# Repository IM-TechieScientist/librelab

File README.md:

# LibreLab

LibreLab is a low-cost, open lab instrument for embedded developers: part logic analyser, part mixed-signal scope, part signal generator, part protocol workbench. The goal is simple: make the kind of debug workflow people buy premium USB instruments for available as open hardware and open software at student/hacker-lab pricing.

Current hardware is targeting a PCB+BOM cost below `₹2500`, roughly `$26.4` at recent INR/USD rates. The next hardware revision is targeting a sub-`$50` build with RP2350B, an AD9629-class high-speed ADC path, HSTX-based high-speed data movement toward a USB 3-class host link, and generous PSRAM buffering.

## Hardware Preview

<table>
  <tr>
    <td width="33%"></td>
    <td width="33%"></td>
    <td width="33%"></td>
  </tr>
  <tr>
    <td align="center">v0.9 board render</td>
    <td align="center">fabricated PCB stack</td>
    <td align="center">PCB top side</td>
  </tr>
</table>

## Software Preview

## Why This Is Interesting

Saleae's current Logic 8 is an 8-channel USB analyser rated at up to 100 MS/s digital capture, 10 MS/s analog capture, 10-bit analog resolution, long PC-streamed captures, 25+ protocol decoders, trigger/search, measurements, automation, and cross-platform software.

LibreLab is aiming at that workflow from the other side of the cost curve:

- `150 MSPS` logic capture on the current RP2350 design path.
- `200 MSPS` logic capture under active development.
- `400 MSPS` burst-mode capture under active development.
- Logic analyser, oscilloscope, mixed-signal capture, pattern generation, test outputs, and bus gateways in one firmware stack.
- USB CDC SCPI today, with optional ESP32-C3 Wi-Fi bridge transport.
- First-party modern desktop software plus PulseView/libsigrok integration for people who prefer the classic sigrok workflow.
- Roadmap hardware aimed at high-speed analog capture and deeper buffering while staying below `$50`.

The bet is that a carefully designed RP2350-class instrument can be brutally useful for firmware bring-up, protocol debugging, education, and small-lab automation without needing a $500-class box on every desk.

## Current Firmware

The firmware lives in [firmware](firmware/) and currently targets Pico 2/RP2350A. Firmware was originally developed by me as part of GSoC 2026.

Implemented so far:

- SCPI 1999-style command interface over USB CDC.
- 1-8 channel PIO/DMA logic analyser.
- One-channel RP2350 internal-ADC oscilloscope path.
- Synchronized mixed-signal one-shot capture.
- 1-8 channel digital pattern generator.
- UART and I2C bus gateways.
- SPI gateway code path, with a known bus-number mismatch still to fix.
- Square-wave and PWM-based analog test outputs.
- ESP32-C3 bridge firmware for TCP SCPI, UDP capture frames, SoftAP provisioning, and mDNS.
- Out-of-tree libsigrok/PulseView driver source.

Useful docs:

- [Firmware README](firmware/README.md)
- [Firmware architecture](firmware/docs/architecture.md)
- [SCPI command reference](firmware/docs/scpi-reference.md)
- [Hardware resources](firmware/docs/hardware.md)
- [RP2350B migration plan](firmware/docs/rp2350b-migration.md)

## Current Software

The desktop application lives in [software](software/) and is built with Electron, React, and TypeScript.

Implemented so far:

- Saleae-style capture workspace with channel rail, session tabs, timeline canvas, and right-side inspector.
- Logic, scope, and mixed-signal modes.
- Deterministic simulator device, so the GUI can be tested without hardware.
- Digital and analog waveform rendering with zoom, pan, fit, hover cursor, and A/B markers.
- Analyzer, measurement, output, and bus-console panels.
- Simulated I2C annotation lane using the same annotation model planned for libsigrokdecode.
- Unit, component, build, and GUI smoke tests.

More:

- [Software README](software/README.md)
- [Software architecture](software/docs/architecture.md)
- [Software feature map](software/docs/features.md)
- [Software testing](software/docs/testing.md)

Run it:

```bash
cd software
npm install
npm run dev
```

Run the browser-rendered GUI for quick UI work:

```bash
cd software
npm run dev:renderer -- --host 127.0.0.1
```

## Hardware Snapshot

The KiCad project lives in [pcb/librelab](pcb/librelab/). The current schematic/PCB includes:

- Raspberry Pi Pico module footprint.
- ESP32-C3-WROOM-02 wireless bridge module.
- AMS1117-3.3 regulator.
- Logic analyser headers.
- Pattern-generator headers.
- ADC headers.
- I2C headers.
- Function/test-output headers.
- Ground headers and reset/boot buttons.
- Generated fabrication outputs under `pcb/librelab/output/`.

## Roadmap

Near-term:

- Connect LibreLab Studio to the real USB SCPI firmware.
- Add capture import/export formats.
- Wire libsigrokdecode into a worker so GUI protocol annotations come from real decoders.
- Finish the SPI gateway bus-number fix.
- Keep PulseView support working alongside the first-party app.

Hardware vNext:

- RP2350B for a cleaner, conflict-free pin map.
- AD9629-class external ADC frontend for serious analog capture.
- HSTX-based high-speed data path toward USB 3-class streaming.
- PSRAM-backed captures and burst buffering.
- 200 MSPS sustained logic capture target and 400 MSPS burst experiments.
- Sub-`$50` target cost.

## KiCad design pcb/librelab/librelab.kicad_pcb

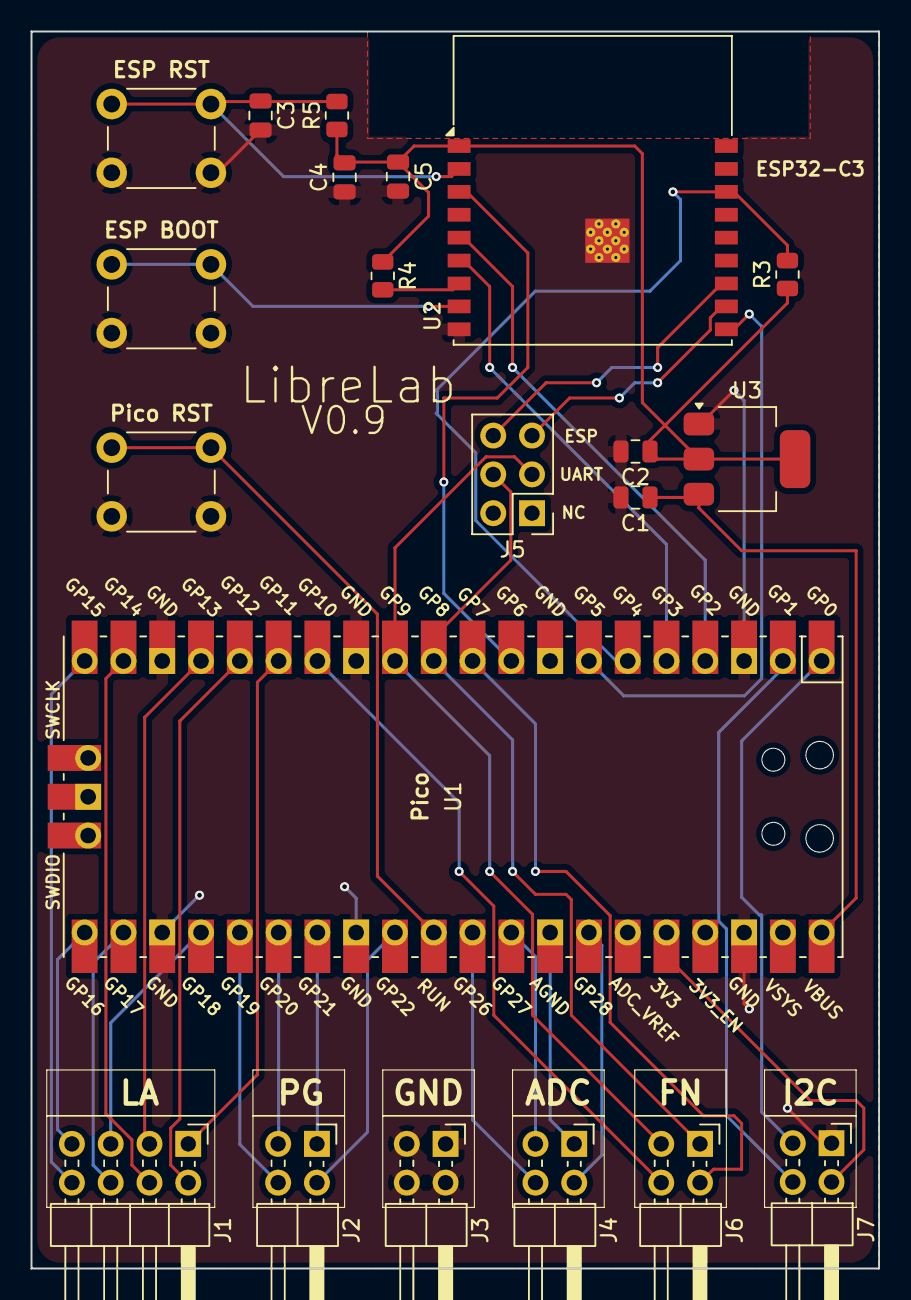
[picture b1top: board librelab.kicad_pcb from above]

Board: 2 copper layers, 55.5 x 81.0 mm, 21 parts (0 on the bottom side), 36 nets.

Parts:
C1, C2, C5: 10uF; C_0805_2012Metric
C3: 1uF; C_0805_2012Metric
C4: 100n; C_0805_2012Metric
ESP BOOT: SW_Push; SW_PUSH_6mm_H5mm
ESP RST: SW_Push; SW_PUSH_6mm_H5mm
J1: LA headers; PinHeader_2x04_P2.54mm_Horizontal
J2: PG headers; PinHeader_2x02_P2.54mm_Horizontal
J3: GND headers; PinHeader_2x02_P2.54mm_Horizontal
J4: ADC headers; PinHeader_2x02_P2.54mm_Horizontal
J5: Conn_02x03_Counter_Clockwise; PinHeader_2x03_P2.54mm_Vertical
J6: FN headers; PinHeader_2x02_P2.54mm_Horizontal
J7: I2C headers; PinHeader_2x02_P2.54mm_Horizontal
Pico RST: SW_Push; SW_PUSH_6mm_H5mm
R3, R4, R5: 10k; R_0805_2012Metric
U1: Pico; RPi_Pico_SMD_TH
U2: ESP32-C3-WROOM-02
U3: AMS1117-3.3; SOT-223-3_TabPin2

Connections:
+3V3: C2.1, C4.2, C5.1, J7.2, R3.1, R4.1, R5.1, U1.36 (3V3), U2.1 (3V3), U3.2 (VO)
+5V: C1.1, U1.40 (VBUS), U3.3 (VI)
/A0: J4.4, U1.31 (GPIO26_ADC0)
/A1: J4.3, U1.32 (GPIO27_ADC1)
/A2: J4.2, U1.34 (GPIO28_ADC2)
/AGND: J4.1, U1.33 (AGND)
/CS: U1.7 (GPIO5), U2.10 (IO10)
/D0: J1.1, U1.15 (GPIO11)
/D1: J1.2, U1.16 (GPIO12)
/D2: J1.3, U1.17 (GPIO13)
/D3: J1.4, U1.19 (GPIO14)
/D4: J1.8, U1.20 (GPIO15)
/D5: J1.7, U1.21 (GPIO16)
/D6: J1.6, U1.22 (GPIO17)
/D7: J1.5, U1.24 (GPIO18)
/D8: J2.4, U1.25 (GPIO19)
/D9: J2.3, U1.26 (GPIO20)
/D10: J2.1, U1.27 (GPIO21)
/D11: J2.2, U1.29 (GPIO22)
/EN: C3.1, ESP RST.1, R5.2, U2.2 (EN)
/IO2: R3.2, U1.6 (GPIO4), U2.16 (IO2)
/IO8: R4.2, U2.7 (IO8)
/IO9: ESP BOOT.1, U2.8 (IO9)
/MOSI: U1.5 (GPIO3), U2.6 (IO7)
/READY: U1.9 (GPIO6), U2.3 (IO4)
/RST: Pico RST.1, U1.30 (RUN)
/RX: J5.3, J6.3, U1.12 (GPIO9)
/RXD: J5.6, U2.12 (IO21/TXD)
/S0: J6.2, U1.10 (GPIO7)
/S1: J6.4, U1.14 (GPIO10)
/SCK: U1.4 (GPIO2), U2.5 (IO6)
/SCL: J7.4, U1.2 (GPIO1)
/SDA: J7.3, U1.1 (GPIO0)
/TX: J5.4, J6.1, U1.11 (GPIO8)
/TXD: J5.5, U2.11 (IO20/RXD)
GND: C1.2, C2.2, C3.2, C4.1, C5.2, ESP BOOT.2, ESP RST.2, J3.1, J3.2, J3.3, J3.4, J7.1, Pico RST.2, U1.3 (GND), U1.13 (GND), U1.18 (GND), U1.23 (GND), U1.28 (GND), U1.38 (GND), U1.42 (GND), U2.9 (GND), U2.19 (GND), U3.1 (GND)

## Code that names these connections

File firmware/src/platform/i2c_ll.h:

/**
 * @file i2c_ll.h
 * @brief Low-level I2C hardware interface for the Raspberry Pi Pico family.
 *
 * This module is the only layer that should call Pico SDK I2C functions
 * directly. System and application code should build on this interface.
 */

#ifndef LIBRELAB_I2C_LL_H
#define LIBRELAB_I2C_LL_H

#include <stdbool.h>
#include <stddef.h>
#include <stdint.h>

#ifdef __cplusplus
extern "C" {
#endif

typedef enum {
    I2C_LL_BUS_0 = 0,
    I2C_LL_BUS_1 = 1,
    I2C_LL_BUS_COUNT = 2,
} I2C_LL_Bus;

enum {
    I2C_LL_DEFAULT_RATE_HZ = 100000,
    I2C_LL_DEFAULT_TIMEOUT_US = 100000,
};

typedef struct {
    uint32_t sda_gpio;
    uint32_t scl_gpio;
    uint32_t rate_hz;
    bool enable_pullups;
} I2C_LL_Config;

/**
 * @brief Fill an I2C configuration with board defaults for a bus.
 *
 * Defaults:
 * - I2C0: SDA GPIO0, SCL GPIO1
 * - I2C1: SDA GPIO6, SCL GPIO7
 * - 100 kHz, internal pull-ups enabled
 */
bool I2C_LL_default_config(I2C_LL_Bus bus, I2C_LL_Config *config);

bool I2C_LL_init(I2C_LL_Bus bus, I2C_LL_Config const *config);
void I2C_LL_deinit(I2C_LL_Bus bus);
bool I2C_LL_is_initialized(I2C_LL_Bus bus);
uint32_t I2C_LL_get_rate(I2C_LL_Bus bus);

int32_t I2C_LL_write(
    I2C_LL_Bus bus,
    uint8_t address,
    uint8_t const *data,
    size_t len,
    bool nostop,
    uint32_t timeout_us
);

int32_t I2C_LL_read(
    I2C_LL_Bus bus,
    uint8_t address,
    uint8_t *data,
    size_t len,
    bool nostop,
    uint32_t timeout_us
);

bool I2C_LL_probe_address(
    I2C_LL_Bus bus,
    uint8_t address,
    uint32_t timeout_us
);

#ifdef __cplusplus
}
#endif

#endif

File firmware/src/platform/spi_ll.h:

/**
 * @file spi_ll.h
 * @brief Low-level SPI hardware interface.
 *
 * This module is the only layer that should call Pico SDK SPI functions
 * directly. System and application code should build on this interface.
 */

#ifndef LIBRELAB_SPI_LL_H
#define LIBRELAB_SPI_LL_H

#include <stdbool.h>
#include <stddef.h>
#include <stdint.h>

#ifdef __cplusplus
extern "C" {
#endif

typedef enum {
    SPI_LL_BUS_1 = 1,
    SPI_LL_BUS_COUNT = 2,
} SPI_LL_Bus;

typedef enum {
    SPI_LL_MODE_0 = 0,
    SPI_LL_MODE_1 = 1,
    SPI_LL_MODE_2 = 2,
    SPI_LL_MODE_3 = 3,
} SPI_LL_Mode;

typedef enum {
    SPI_LL_BIT_ORDER_MSB_FIRST = 0,
    SPI_LL_BIT_ORDER_LSB_FIRST = 1,
} SPI_LL_BitOrder;

enum {
    SPI_LL_DEFAULT_RATE_HZ = 1000000,
};

typedef struct {
    uint32_t sck_gpio;
    uint32_t tx_gpio;
    uint32_t rx_gpio;
    uint32_t cs_gpio;
    uint32_t rate_hz;
    SPI_LL_Mode mode;
    SPI_LL_BitOrder bit_order;
    bool cs_active_low;
} SPI_LL_Config;

/**
 * @brief Fill an SPI configuration with board defaults for a bus.
 *
 * Defaults:
 * - SPI1: SCK GPIO10, TX/MOSI GPIO11, RX/MISO GPIO12, CS GPIO13
 * - 1 MHz, mode 0, MSB first, active-low CS
 *
 * SPI0 is intentionally not exposed by this platform interface as
 * it is currently being used by the ESP/WiFi bridge.
 */
bool SPI_LL_default_config(SPI_LL_Bus bus, SPI_LL_Config *config);

bool SPI_LL_init(SPI_LL_Bus bus, SPI_LL_Config const *config);
void SPI_LL_deinit(SPI_LL_Bus bus);
bool SPI_LL_is_initialized(SPI_LL_Bus bus);
uint32_t SPI_LL_get_rate(SPI_LL_Bus bus);
SPI_LL_Mode SPI_LL_get_mode(SPI_LL_Bus bus);
SPI_LL_BitOrder SPI_LL_get_bit_order(SPI_LL_Bus bus);

bool SPI_LL_select(SPI_LL_Bus bus);
void SPI_LL_deselect(SPI_LL_Bus bus);
bool SPI_LL_is_selected(SPI_LL_Bus bus);

int32_t SPI_LL_transfer(
    SPI_LL_Bus bus,
    uint8_t const *tx_data,
    uint8_t *rx_data,
    size_t len,
    uint8_t dummy_byte
);

#ifdef __cplusplus
}
#endif

#endif
